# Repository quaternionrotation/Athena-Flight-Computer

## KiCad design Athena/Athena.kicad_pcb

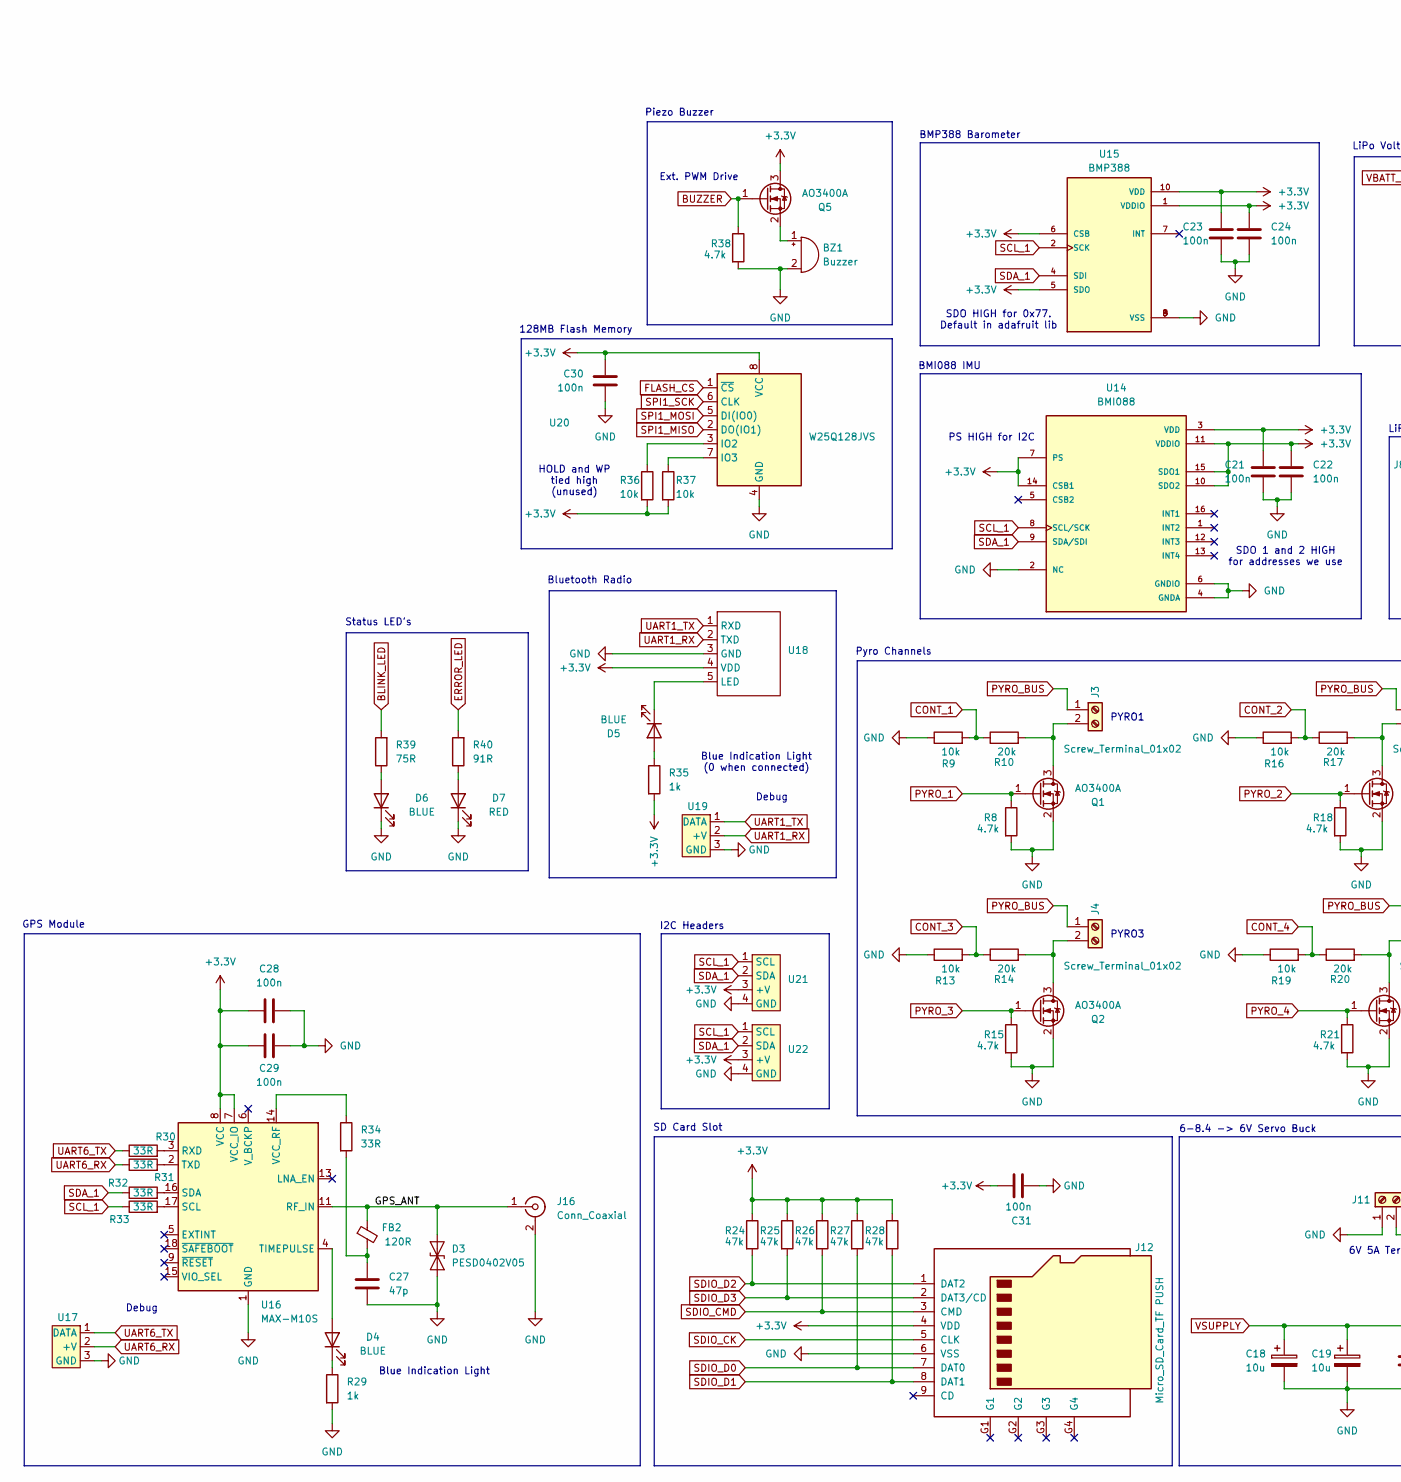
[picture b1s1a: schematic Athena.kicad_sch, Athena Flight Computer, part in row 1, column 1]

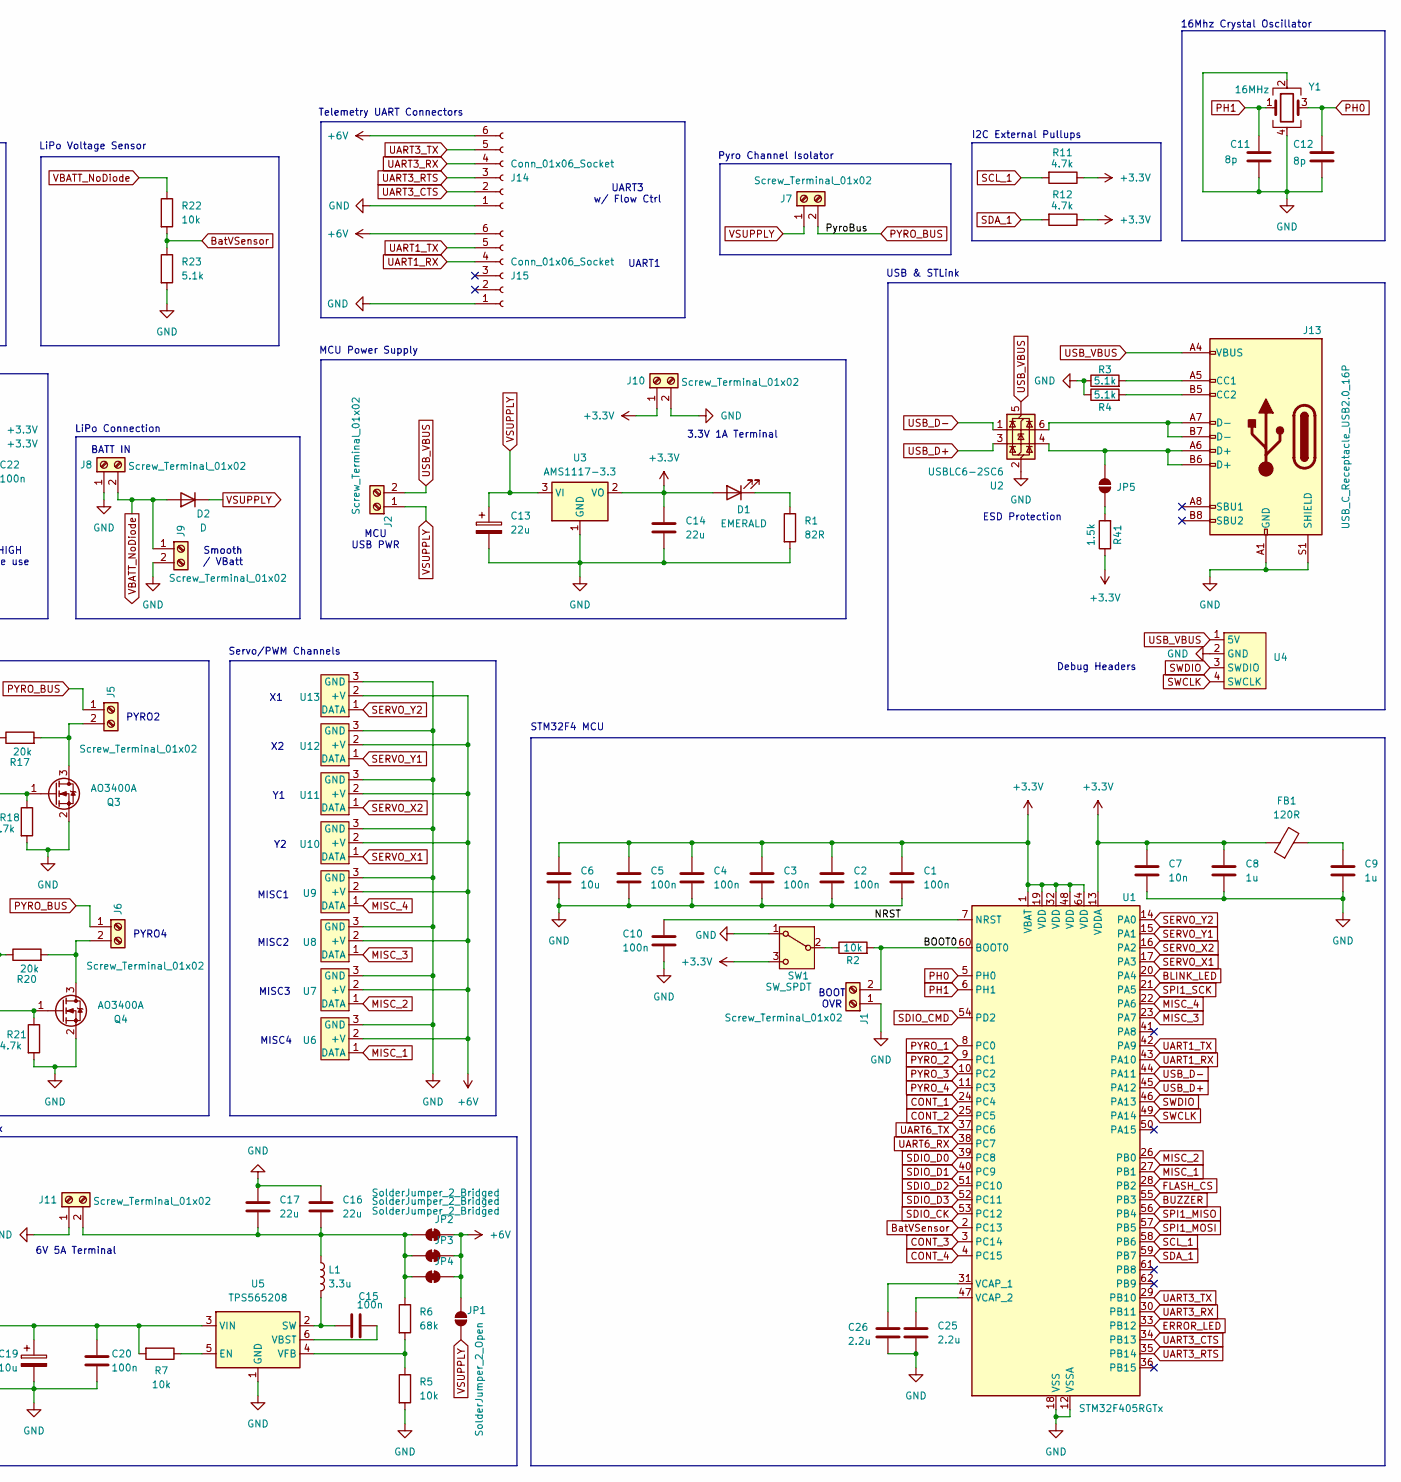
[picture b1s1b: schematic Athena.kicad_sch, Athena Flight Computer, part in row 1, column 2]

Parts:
BZ1: Buzzer; Buzzer_TDK_PS1240P02BT_D12.2mm_H6.5mm
C1, C2, C3, C4, C5, C10, C15, C20, C21, C22, C23, C24, C28, C29, C30, C31: 100n; C_0603_1608Metric
C6: 10u; C_0603_1608Metric
C7: 10n; C_0603_1608Metric
C8, C9: 1u; C_0603_1608Metric
C11, C12: 8p; C_0603_1608Metric
C13: 22u; CP_EIA-3216-10_Kemet-I
C14, C16, C17: 22u; C_0603_1608Metric
C18, C19: 10u; CP_EIA-3528-12_Kemet-T
C25, C26: 2.2u; C_0603_1608Metric
C27: 47p; C_0603_1608Metric
D1: EMERALD; LED_0805_2012Metric
D2: D; D_SMB
D3: PESD0402V05; D_0402_1005Metric
D4, D5, D6: BLUE; LED_0603_1608Metric
D7: RED; LED_0603_1608Metric
FB1, FB2: 120R; L_0603_1608Metric
J1, J2, J3, J4, J5, J6, J7, J8, J9, J10, J11: Screw_Terminal_01x02; TerminalBlock_bornier-2_P5.08mm
J12: Micro_SD_Card_TF PUSH; SUNTECH_ST-TF-003A
J13: USB_C_Receptacle_USB2.0_16P; USB_C_Receptacle_GCT_USB4105-xx-A_16P_TopMnt_Horizontal
J14, J15: Conn_01x06_Socket; JST_GH_SM06B-GHS-TB_1x06-1MP_P1.25mm_Horizontal
J16: Conn_Coaxial; U.FL_Hirose_U.FL-R-SMT-1_Vertical
JP1, JP5: SolderJumper_2_Open; SolderJumper-2_P1.3mm_Open_Pad1.0x1.5mm
JP2, JP3, JP4: SolderJumper_2_Bridged; SolderJumper-2_P1.3mm_Bridged_Pad1.0x1.5mm
L1: 3.3u; IND_CYA0630_SHH
Q1, Q2, Q3, Q4, Q5: AO3400A; SOT-23
R1: 82R; R_0603_1608Metric
R2, R5, R7, R9, R13, R16, R19, R22, R36, R37: 10k; R_0603_1608Metric
R3, R4, R23: 5.1k; R_0603_1608Metric
R6: 68k; R_0603_1608Metric
R8, R11, R12, R15, R18, R21, R38: 4.7k; R_0603_1608Metric
R10, R14, R17, R20: 20k; R_0603_1608Metric
R24, R25, R26, R27, R28: 47k; R_0603_1608Metric
R29, R35: 1k; R_0603_1608Metric
R30, R31, R32, R33, R34: 33R; R_0603_1608Metric
R39: 75R; R_0603_1608Metric
R40: 91R; R_0603_1608Metric
R41: 1.5k; R_0603_1608Metric
SW1: SW_SPDT; SW_SS12D07VG4
U1: STM32F405RGTx; LQFP-64_10x10mm_P0.5mm
U2: USBLC6-2SC6; SOT-23-6
U3: AMS1117-3.3; SOT-223-3_TabPin2
U4, U21, U22: PinHeader_1x04_P2.54mm_Vertical
U5: TPS565208; SOT-23-6
U6, U7, U8, U9, U10, U11, U12, U13, U17, U19: PinHeader_1x03_P2.54mm_Vertical
U14: BMI088; PQFN50P450X300X100-16N
U15: BMP388; PQFN50P200X200X80-10N; PARTREV 1.1
U16: MAX-M10S; ublox_MAX
U18: VG6328A
U20: W25Q128JVS; SOIC-8_5.23x5.23mm_P1.27mm
Y1: 16MHz; Crystal_SMD_SeikoEpson_TSX3225-4Pin_3.2x2.5mm

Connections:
+3.3V: C1.1, C2.1, C3.1, C4.1, C5.1, C6.1, C7.1, C8.1, C14.1, C21.1, C22.1, C23.1, C24.1, C28.1, C29.1, C30.1, C31.1, D1.2 (A), FB1.1, J10.1, J12.4 (VDD), Q5.3 (D), R11.1, R12.1, R24.1, R25.1, R26.1, R27.1, R28.1, R35.2, R36.2, R37.2, R41.1, SW1.3 (C), U1.1 (VBAT), U1.13 (VDDA), U1.19 (VDD), U1.32 (VDD), U1.48 (VDD), U1.64 (VDD), U3.2 (VO), U14.3 (VDD), U14.7 (PS), U14.10 (SDO2), U14.11 (VDDIO), U14.14 (CSB1), U14.15 (SDO1), U15.1 (VDDIO), U15.5 (SDO), U15.6 (CSB), U15.10 (VDD), U16.7 (VCC_IO), U16.8 (VCC), U18.4 (VDD), U20.8 (VCC), U21.3 (+V), U22.3 (+V)
+6V: J14.6, J15.6, JP1.2 (B), JP2.2 (B), JP3.2 (B), JP4.2 (B), U6.2 (+V), U7.2 (+V), U8.2 (+V), U9.2 (+V), U10.2 (+V), U11.2 (+V), U12.2 (+V), U13.2 (+V)
/BOOT0: J1.2, R2.2, U1.60 (BOOT0)
/GPS_ANT: D3.1 (A1), FB2.1, J16.1 (In), U16.11 (RF_IN)
/NRST: C10.1, U1.7 (NRST)
BLINK_LED: R39.2, U1.20 (PA4)
BUZZER: Q5.1 (G), R38.1, U1.55 (PB3)
BatVSensor: R22.2, R23.1, U1.2 (PC13)
CONT_1: R9.2, R10.1, U1.24 (PC4)
CONT_2: R16.2, R17.1, U1.25 (PC5)
CONT_3: R13.2, R14.1, U1.3 (PC14)
CONT_4: R19.2, R20.1, U1.4 (PC15)
ERROR_LED: R40.2, U1.33 (PB12)
FLASH_CS: U1.28 (PB2), U20.1 (~CS)
GND: BZ1.2 (-), C1.2, C2.2, C3.2, C4.2, C5.2, C6.2, C7.2, C8.2, C9.2, C10.2, C11.2, C12.2, C13.2, C14.2, C16.1, C17.1, C18.2, C19.2, C20.2, C21.2, C22.2, C23.2, C24.2, C25.2, C26.2, C27.2, C28.2, C29.2, C30.2, C31.2, D3.2 (A2), D6.1 (K), D7.1 (K), J1.1, J8.1, J9.2, J10.2, J11.1, J12.6 (VSS), J13.A1 (GND), J13.A12 (GND), J13.B1 (GND), J13.B12 (GND), J13.S1 (SHIELD), J14.1, J15.1, J16.2 (Ext), Q1.2 (S), Q2.2 (S), Q3.2 (S), Q4.2 (S), R1.2, R3.1, R4.1, R5.2, R8.2, R9.1, R13.1, R15.2, R16.1, R18.2, R19.1, R21.2, R23.2, R29.2, R38.2, SW1.1 (A), U1.12 (VSSA), U1.18 (VSS), U1.63 (VSS), U2.2 (GND), U3.1 (GND), U4.2 (GND), U5.1 (GND), U6.3 (GND), U7.3 (GND), U8.3 (GND), U9.3 (GND), U10.3 (GND), U11.3 (GND), U12.3 (GND), U13.3 (GND), U14.2 (NC), U14.4 (GNDA), U14.6 (GNDIO), U15.3 (VSS), U15.8 (VSS), U15.9 (VSS), U16.1 (GND), U16.10 (GND), U16.12 (GND), U17.3 (GND), U18.3 (GND), U19.3 (GND), U20.4 (GND), U21.4 (GND), U22.4 (GND), Y1.2, Y1.4
MISC_1: U1.27 (PB1), U6.1 (DATA)
MISC_2: U1.26 (PB0), U7.1 (DATA)
MISC_3: U1.23 (PA7), U8.1 (DATA)
MISC_4: U1.22 (PA6), U9.1 (DATA)
unnamed: BZ1.1 (+), Q5.2 (S)
unnamed: C9.1, FB1.2
unnamed: C27.1, FB2.2, R34.2
unnamed: D1.1 (K), R1.1
unnamed: D4.2 (A), U16.4 (TIMEPULSE)
unnamed: D4.1 (K), R29.1
unnamed: D5.2 (A), R35.1
unnamed: D5.1 (K), U18.5 (LED)
unnamed: D6.2 (A), R39.1
unnamed: D7.2 (A), R40.1
unnamed: J3.2, Q1.3 (D), R10.2
unnamed: J4.2, Q2.3 (D), R14.2
unnamed: J5.2, Q3.3 (D), R17.2
unnamed: J6.2, Q4.3 (D), R20.2
unnamed: C16.2, C17.2, J11.2, JP2.1 (A), JP3.1 (A), JP4.1 (A), L1.1, R6.1
unnamed: J13.A5 (CC1), R3.2
unnamed: J13.B5 (CC2), R4.2
unnamed: J13.A7 (D-), J13.B7 (D-), U2.6 (I/O1)
unnamed: JP5.1 (A), R41.2
unnamed: J13.A6 (D+), J13.B6 (D+), JP5.2 (B), U2.4 (I/O2)
unnamed: R2.1, SW1.2 (B)
unnamed: C26.1, U1.31 (VCAP_1)
unnamed: C25.1, U1.47 (VCAP_2)
unnamed: R7.1, U5.5 (EN)
unnamed: C15.1, L1.2, U5.2 (SW)
unnamed: C15.2, U5.6 (VBST)
unnamed: R5.1, R6.2, U5.4 (VFB)
unnamed: R30.2, U16.3 (RXD)
unnamed: R33.2, U16.17 (SCL)
unnamed: R32.2, U16.16 (SDA)
unnamed: R31.2, U16.2 (TXD)
unnamed: R34.1, U16.14 (VCC_RF)
unnamed: R36.1, U20.3 (IO2)
unnamed: R37.1, U20.7 (IO3)
PH0: C12.1, U1.5 (PH0), Y1.3
PH1: C11.1, U1.6 (PH1), Y1.1
PYRO_1: Q1.1 (G), R8.1, U1.8 (PC0)
PYRO_2: Q3.1 (G), R18.1, U1.9 (PC1)
PYRO_3: Q2.1 (G), R15.1, U1.10 (PC2)
PYRO_4: Q4.1 (G), R21.1, U1.11 (PC3)
PYRO_BUS: J3.1, J4.1, J5.1, J6.1, J7.2
SCL_1: R11.2, R33.1, U1.58 (PB6), U14.8 (SCL/SCK), U15.2 (SCK), U21.1 (SCL), U22.1 (SCL)
SDA_1: R12.2, R32.1, U1.59 (PB7), U14.9 (SDA/SDI), U15.4 (SDI), U21.2 (SDA), U22.2 (SDA)
SDIO_CK: J12.5 (CLK), U1.53 (PC12)
SDIO_CMD: J12.3 (CMD), R26.2, U1.54 (PD2)
SDIO_D0: J12.7 (DAT0), R27.2, U1.39 (PC8)
SDIO_D1: J12.8 (DAT1), R28.2, U1.40 (PC9)
SDIO_D2: J12.1 (DAT2), R24.2, U1.51 (PC10)
SDIO_D3: J12.2 (DAT3/CD), R25.2, U1.52 (PC11)
SERVO_X1: U1.17 (PA3), U10.1 (DATA)
SERVO_X2: U1.16 (PA2), U11.1 (DATA)
SERVO_Y1: U1.15 (PA1), U12.1 (DATA)
SERVO_Y2: U1.14 (PA0), U13.1 (DATA)
SPI1_MISO: U1.56 (PB4), U20.2 (DO(IO1))
SPI1_MOSI: U1.57 (PB5), U20.5 (DI(IO0))
SPI1_SCK: U1.21 (PA5), U20.6 (CLK)
SWCLK: U1.49 (PA14), U4.4 (SWCLK)
SWDIO: U1.46 (PA13), U4.3 (SWDIO)
UART1_RX: J15.4, U1.43 (PA10), U18.2 (TXD), U19.2 (+V)
UART1_TX: J15.5, U1.42 (PA9), U18.1 (RXD), U19.1 (DATA)
UART3_CTS: J14.2, U1.34 (PB13)
UART3_RTS: J14.3, U1.35 (PB14)
UART3_RX: J14.4, U1.30 (PB11)
UART3_TX: J14.5, U1.29 (PB10)
UART6_RX: R31.1, U1.38 (PC7), U17.2 (+V)
UART6_TX: R30.1, U1.37 (PC6), U17.1 (DATA)
USB_D+: U1.45 (PA12), U2.3 (I/O2)
USB_D-: U1.44 (PA11), U2.1 (I/O1)
USB_VBUS: J2.2, J13.A4 (VBUS), J13.A9 (VBUS), J13.B4 (VBUS), J13.B9 (VBUS), U2.5 (VBUS), U4.1 (5V)
VBATT_NoDiode: D2.2 (A), J8.2, J9.1, R22.1
VSUPPLY: C13.1, C18.1, C19.1, C20.1, D2.1 (K), J2.1, J7.1, JP1.1 (A), R7.2, U3.3 (VI), U5.3 (VIN)

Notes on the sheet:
I2C Headers
LiPo Connection
6V 5A Terminal
Telemetry UART Connectors
BATT IN
Piezo Buzzer
16Mhz Crystal Oscillator
Pyro Channels
128MB Flash Memory
Bluetooth Radio
BOOT OVR
UART1
PYRO3
LiPo Voltage Sensor
MCU Power Supply
I2C External Pullups
SDO HIGH for 0x77. Default in adafruit lib
PYRO4
Debug
HOLD and WP tied high (unused)
Blue Indication Light
ESD Protection
Ext. PWM Drive
GPS Module
Status LED's
BMI088 IMU
6-8.4 -> 6V Servo Buck
Blue Indication Light (0 when connected)
PYRO1
3.3V 1A Terminal
SDO 1 and 2 HIGH for addresses we use
STM32F4 MCU
UART3 w/ Flow Ctrl
Debug Headers
MISC2
MISC4
PYRO2
MISC3
Pyro Channel Isolator
MISC1

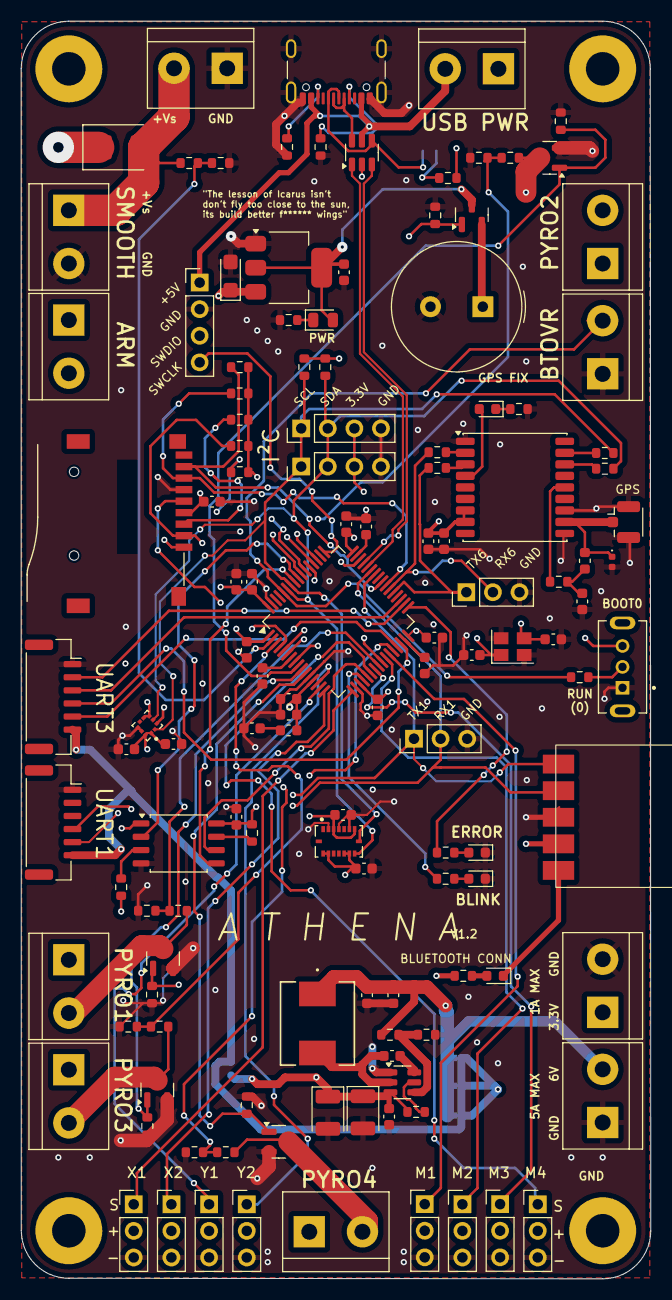
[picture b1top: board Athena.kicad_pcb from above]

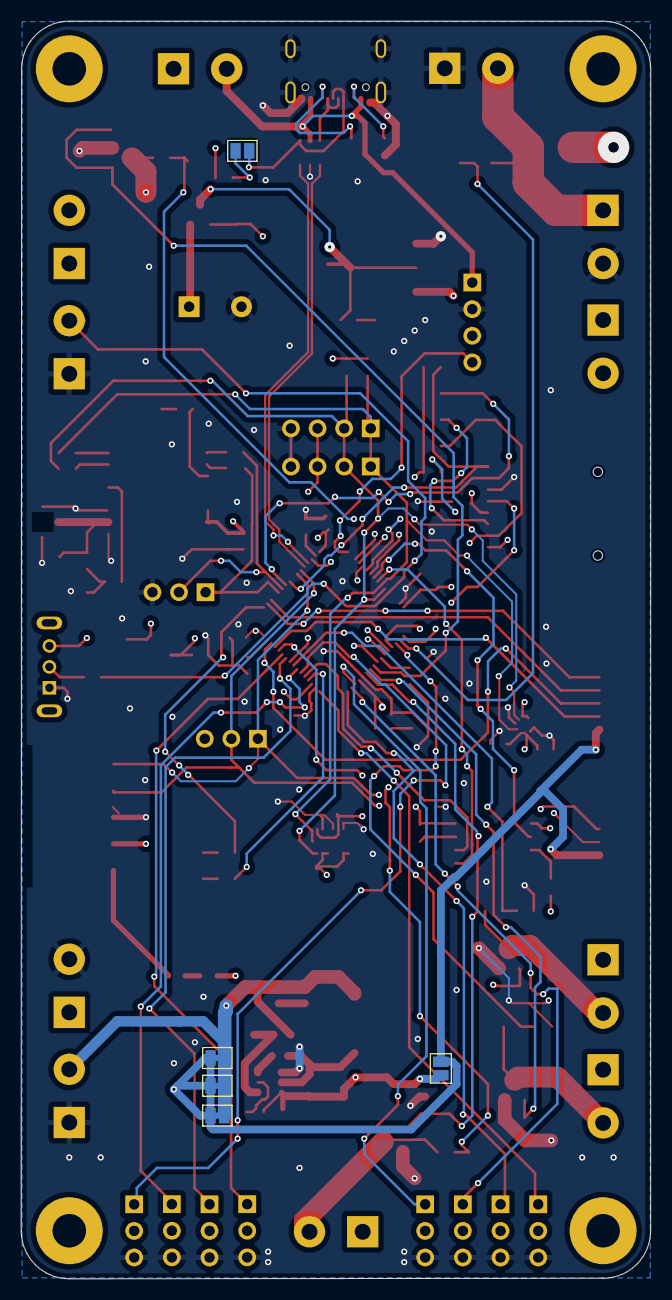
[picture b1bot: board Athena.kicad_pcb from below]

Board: 4 copper layers, 60.1 x 120.1 mm, 133 parts (5 on the bottom side), 90 nets.

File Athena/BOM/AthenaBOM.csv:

Designator,Comment,Footprint,Qty,JLCPCB Part #
BZ1,Buzzer,Buzzer_Beeper:Buzzer_TDK_PS1240P02BT_D12.2mm_H6.5mm,1,C76873
"C1,C2,C3,C4,C5,C10,C15,C20,C21,C22,C23,C24,C28,C29,C30,C31",100n,Capacitor_SMD:C_0603_1608Metric,16,C14663
C6,10u,Capacitor_SMD:C_0603_1608Metric,1,C1691
C7,10n,Capacitor_SMD:C_0603_1608Metric,1,C1589
"C8,C9",1u,Capacitor_SMD:C_0603_1608Metric,2,C1592
"C11,C12",8p,Capacitor_SMD:C_0603_1608Metric,2,C36508
"C14,C16,C17",22u,Capacitor_SMD:C_0603_1608Metric,4,C59461
"C25,C26",2.2u,Capacitor_SMD:C_0603_1608Metric,2,C1607
C27,47p,Capacitor_SMD:C_0603_1608Metric,1,C1671
D1,EMERALD,LED_SMD:LED_0805_2012Metric,1,C2297
D2,D,Diode_SMD:D_SMB,1,C18199105
D3,PESD0402V05,Diode_SMD:D_0402_1005Metric,1,C19626254
"D4,D5,D6",BLUE,LED_SMD:LED_0603_1608Metric,3,C2288
D7,RED,LED_SMD:LED_0603_1608Metric,1, C2286
"FB1,FB2",120R,Inductor_SMD:L_0603_1608Metric,2,C14709
J12,Micro_SD_Card_TF PUSH,ST-TF-003A:SUNTECH_ST-TF-003A,1,C393941
J13,USB_C_Receptacle_USB2.0_16P,Connector_USB:USB_C_Receptacle_GCT_USB4105-xx-A_16P_TopMnt_Horizontal,1,C2765186
"J14,J15",Conn_01x06_Socket,Connector_JST:JST_GH_SM06B-GHS-TB_1x06-1MP_P1.25mm_Horizontal,2,C133065
J16,Conn_Coaxial,Connector_Coaxial:U.FL_Hirose_U.FL-R-SMT-1_Vertical,1,C5137195
L1,3.3u,CYA0630-3.3UH:IND_CYA0630_SHH,1,C5189747
"Q1,Q2,Q3,Q4,Q5",AO3400A,Package_TO_SOT_SMD:SOT-23,5,C20917
R1,82R,Resistor_SMD:R_0603_1608Metric,1,C23255
"R2,R5,R7,R9,R13,R16,R19,R22,R36,R37",10k,Resistor_SMD:R_0603_1608Metric,10,C25804
"R3,R4,R23",5.1k,Resistor_SMD:R_0603_1608Metric,3,C23186
R6,68k,Resistor_SMD:R_0603_1608Metric,1,C23231
"R8,R11,R12,R15,R18,R21,R38",4.7k,Resistor_SMD:R_0603_1608Metric,7,C23162
"R10,R14,R17,R20",20k,Resistor_SMD:R_0603_1608Metric,4,C4184
"R24,R25,R26,R27,R28",47k,Resistor_SMD:R_0603_1608Metric,5,C25600
"R29,R35",1k,Resistor_SMD:R_0603_1608Metric,2,C21190
"R30,R31,R32,R33,R34",33R,Resistor_SMD:R_0603_1608Metric,5,C23140
R39,75R,Resistor_SMD:R_0603_1608Metric,1,C4275
R40,91R,Resistor_SMD:R_0603_1608Metric,1,C25199
SW1,SW_SPDT,SS12D07VG4:SW_SS12D07VG4,1,C2939728
U1,STM32F405RGTx,Package_QFP:LQFP-64_10x10mm_P0.5mm,1,C15742 
U2,USBLC6-2SC6,Package_TO_SOT_SMD:SOT-23-6,1,C7519
U3,AMS1117-3.3,Package_TO_SOT_SMD:SOT-223-3_TabPin2,1,C6186
U18,BLUETOOTH,bluetooth:VG6328A,1,C20539408
U5,TPS565208,Package_TO_SOT_SMD:SOT-23-6,1,C327676
U20,W25Q128JVS,Package_SO:SOIC-8_5.23x5.23mm_P1.27mm,1,C97521
Y1,16MHz,Crystal:Crystal_SMD_SeikoEpson_TSX3225-4Pin_3.2x2.5mm,1,C13738
U14,BMI088,BMI088:PQFN50P450X300X100-16N,1,C194919
U15,BMP388,BMP388:PQFN50P200X200X80-10N,1,C779278
R41,1.5k,Resistor_SMD:R_0603_1608Metric,1,C22843
"C18, C19",10u,CASE-B-3528-19(mm),2,C128259
C13,22u,CASE-A-3216-16(mm),1,C129272
"R42,R43",22R,Resistor_SMD:R_0603_1608Metric,2,C23345

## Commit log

2025-09-25 Fixed NASA Worm Font
2025-09-25 updated schematic to KiCad 9
2025-09-25 fixed it
